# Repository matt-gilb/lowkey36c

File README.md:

# lowkey36c
Repo for docs, PCB, and case for the LowKey36 Choc v1

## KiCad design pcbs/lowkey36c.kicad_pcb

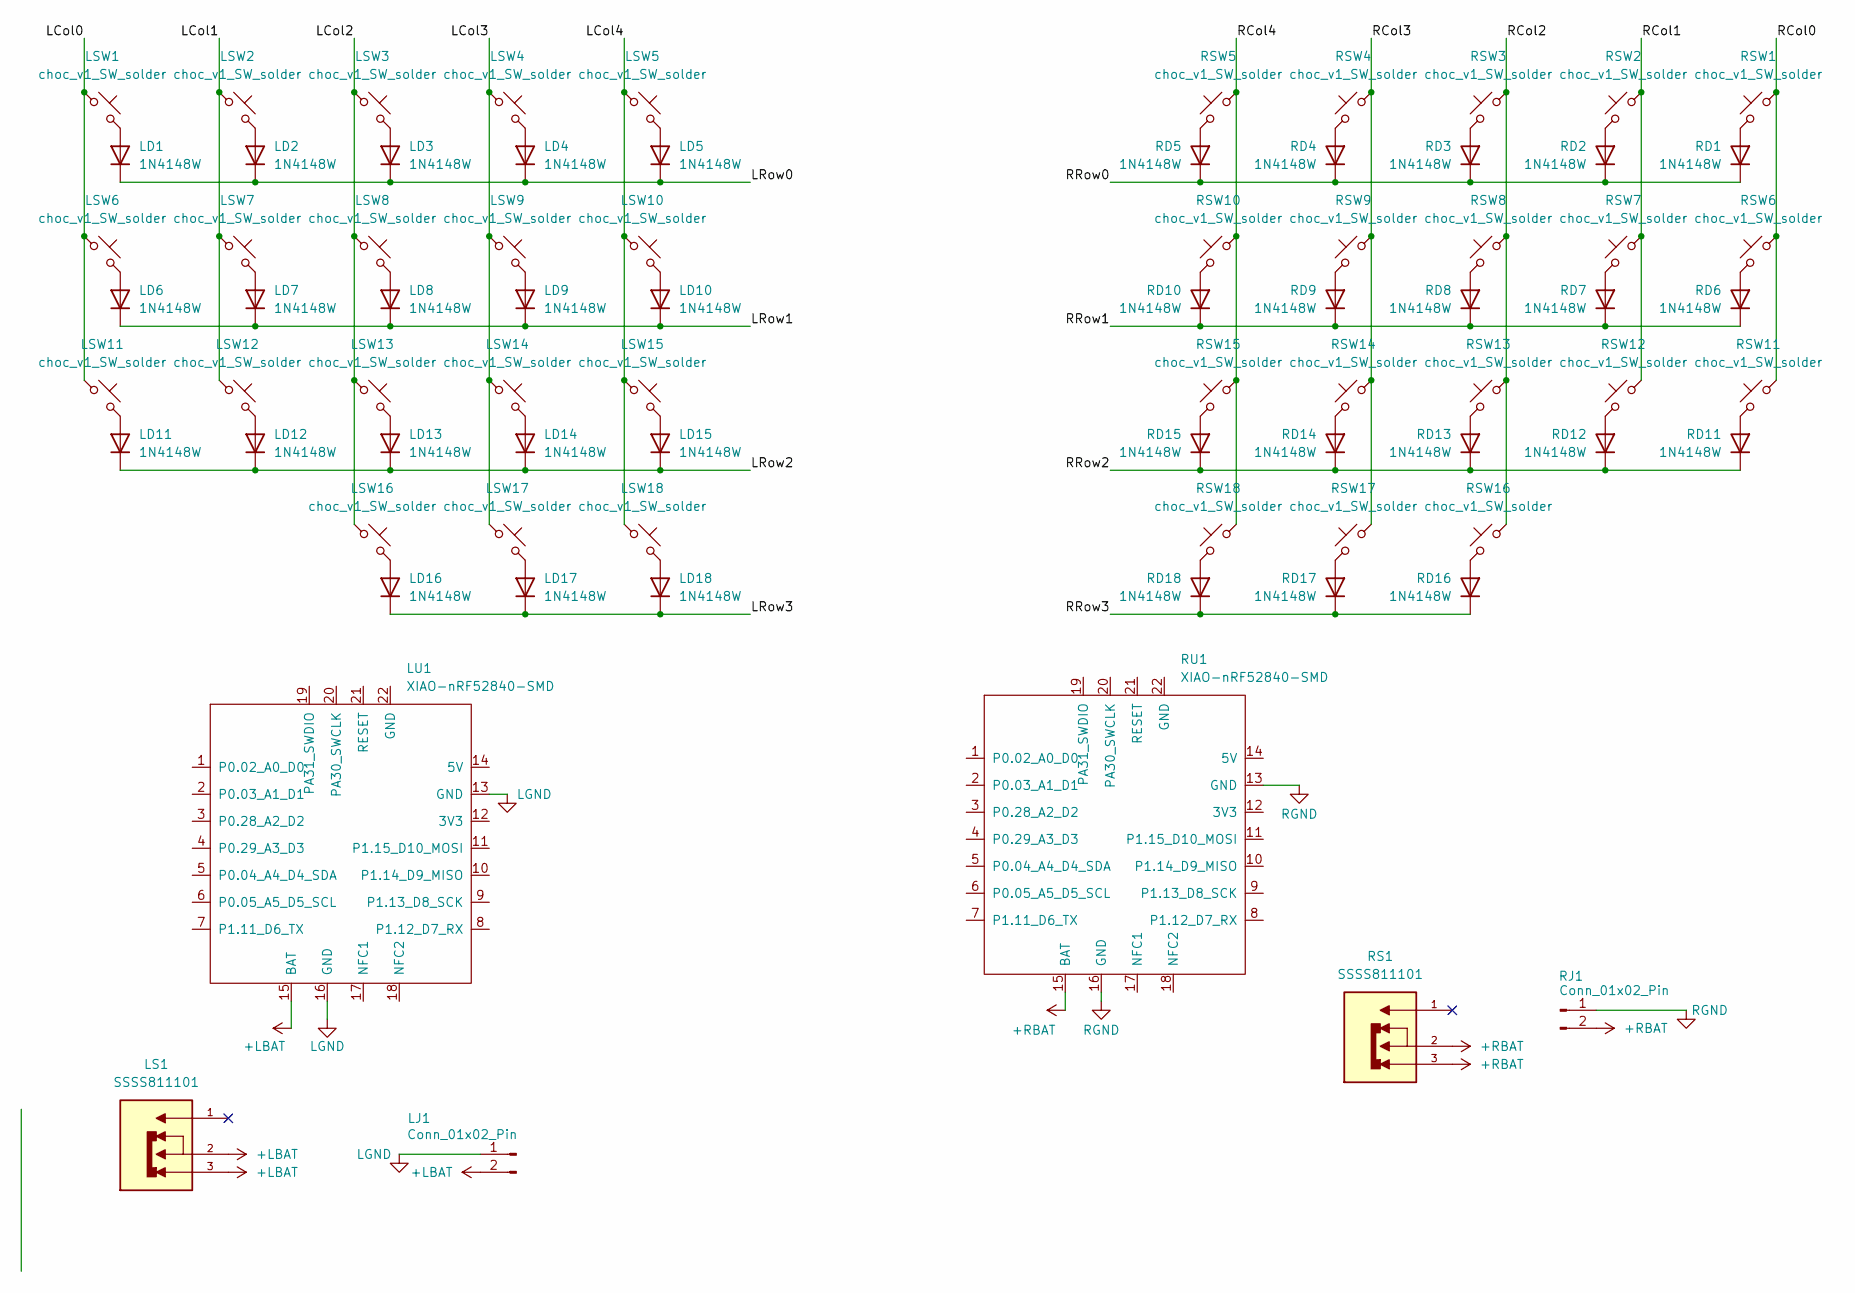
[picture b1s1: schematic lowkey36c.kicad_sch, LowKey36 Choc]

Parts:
LD1, LD2, LD3, LD4, LD5, LD6, LD7, LD8, LD9, LD10, LD11, LD12, LD13, LD14, LD15, LD16, LD17, LD18: 1N4148W; D_SOD-123
LJ1: Conn_01x02_Pin; SolderWire-0.1sqmm_1x02_P3.6mm_D0.4mm_OD1mm
LS1: SSSS811101; SW_SSSS811101; PARTREV N/A
LSW1, LSW2, LSW3, LSW4, LSW5, LSW6, LSW7, LSW8, LSW9, LSW10, LSW11, LSW12, LSW13, LSW14, LSW15, LSW16: choc_v1_SW_solder; SW_choc_v1_1u
LSW17, LSW18: choc_v1_SW_solder; SW_choc_v1_1.5u
LU1: XIAO-nRF52840-SMD; xiao-ble-smd-cutout
RD1, RD2, RD3, RD4, RD5, RD6, RD7, RD8, RD9, RD10, RD11, RD12, RD13, RD14, RD15, RD16, RD17, RD18: 1N4148W; D_SOD-123
RJ1: Conn_01x02_Pin; SolderWire-0.1sqmm_1x02_P3.6mm_D0.4mm_OD1mm
RS1: SSSS811101; SW_SSSS811101; PARTREV N/A
RSW1, RSW2, RSW3, RSW4, RSW5, RSW6, RSW7, RSW8, RSW9, RSW10, RSW11, RSW12, RSW13, RSW14, RSW15, RSW16: choc_v1_SW_solder; SW_choc_v1_1u
RSW17, RSW18: choc_v1_SW_solder; SW_choc_v1_1.5u
RU1: XIAO-nRF52840-SMD; xiao-ble-smd-cutout

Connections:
+LBAT: LJ1.2, LS1.2, LS1.3, LU1.15 (BAT)
+RBAT: RJ1.2, RS1.2, RS1.3, RU1.15 (BAT)
/LCol0: LSW1.1, LSW6.1, LSW11.1
/LCol1: LSW2.1, LSW7.1, LSW12.1
/LCol2: LSW3.1, LSW8.1, LSW13.1, LSW16.1
/LCol3: LSW4.1, LSW9.1, LSW14.1, LSW17.1
/LCol4: LSW5.1, LSW10.1, LSW15.1, LSW18.1
/LRow0: LD1.1 (K), LD2.1 (K), LD3.1 (K), LD4.1 (K), LD5.1 (K)
/LRow1: LD6.1 (K), LD7.1 (K), LD8.1 (K), LD9.1 (K), LD10.1 (K)
/LRow2: LD11.1 (K), LD12.1 (K), LD13.1 (K), LD14.1 (K), LD15.1 (K)
/LRow3: LD16.1 (K), LD17.1 (K), LD18.1 (K)
/RCol0: RSW1.1, RSW6.1, RSW11.1
/RCol1: RSW2.1, RSW7.1, RSW12.1
/RCol2: RSW3.1, RSW8.1, RSW13.1, RSW16.1
/RCol3: RSW4.1, RSW9.1, RSW14.1, RSW17.1
/RCol4: RSW5.1, RSW10.1, RSW15.1, RSW18.1
/RRow0: RD1.1 (K), RD2.1 (K), RD3.1 (K), RD4.1 (K), RD5.1 (K)
/RRow1: RD6.1 (K), RD7.1 (K), RD8.1 (K), RD9.1 (K), RD10.1 (K)
/RRow2: RD11.1 (K), RD12.1 (K), RD13.1 (K), RD14.1 (K), RD15.1 (K)
/RRow3: RD16.1 (K), RD17.1 (K), RD18.1 (K)
LGND: LJ1.1, LU1.13 (GND), LU1.16 (GND); also elsewhere on the board
unnamed: LD1.2 (A), LSW1.2
unnamed: LD2.2 (A), LSW2.2
unnamed: LD3.2 (A), LSW3.2
unnamed: LD4.2 (A), LSW4.2
unnamed: LD5.2 (A), LSW5.2
unnamed: LD6.2 (A), LSW6.2
unnamed: LD7.2 (A), LSW7.2
unnamed: LD8.2 (A), LSW8.2
unnamed: LD9.2 (A), LSW9.2
unnamed: LD10.2 (A), LSW10.2
unnamed: LD11.2 (A), LSW11.2
unnamed: LD12.2 (A), LSW12.2
unnamed: LD13.2 (A), LSW13.2
unnamed: LD14.2 (A), LSW14.2
unnamed: LD15.2 (A), LSW15.2
unnamed: LD16.2 (A), LSW16.2
unnamed: LD17.2 (A), LSW17.2
unnamed: LD18.2 (A), LSW18.2
unnamed: RD1.2 (A), RSW1.2
unnamed: RD2.2 (A), RSW2.2
unnamed: RD3.2 (A), RSW3.2
unnamed: RD4.2 (A), RSW4.2
unnamed: RD5.2 (A), RSW5.2
unnamed: RD6.2 (A), RSW6.2
unnamed: RD7.2 (A), RSW7.2
unnamed: RD8.2 (A), RSW8.2
unnamed: RD9.2 (A), RSW9.2
unnamed: RD10.2 (A), RSW10.2
unnamed: RD11.2 (A), RSW11.2
unnamed: RD12.2 (A), RSW12.2
unnamed: RD13.2 (A), RSW13.2
unnamed: RD14.2 (A), RSW14.2
unnamed: RD15.2 (A), RSW15.2
unnamed: RD16.2 (A), RSW16.2
unnamed: RD17.2 (A), RSW17.2
unnamed: RD18.2 (A), RSW18.2
RGND: RJ1.1, RU1.13 (GND), RU1.16 (GND); also elsewhere on the board

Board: 2 copper layers, 84 parts (2 on the bottom side), 58 nets, no tracks yet.

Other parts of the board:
LMH1, LMH2, LMH3: MountingHole_2.2mm_M2_DIN965_Pad_TopBottom
RMH1, RMH2, RMH3: MountingHole_2.2mm_M2_DIN965_Pad_TopBottom

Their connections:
LGND: LMH1.1, LMH2.1, LMH3.1; also elsewhere on the board
RGND: RMH1.1, RMH2.1, RMH3.1; also elsewhere on the board

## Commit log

2024-12-21 kicad files added
2024-12-22 add component submodules and update pcb files

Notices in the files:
pcbs/lowkey36c.kicad_sch:
© Matt Gilbert
